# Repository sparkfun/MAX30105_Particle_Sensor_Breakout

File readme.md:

MAX30105 Particle and Pulse Ox Sensor Breakout
=======

A breakout board for the MAX30105 Particle Sensor. This sensor uses three LEDs (Red, Green, IR) to shine different wavelengths of light at any particle in front of the photo detector. Based on the reflection the sensor outputs readings. 

That's my heart beat!

Sensor is capable of detecting pulses but only limited algorithms are provided. It is up to the user to create the algorithms to detect different particles and/or SPO2 and/or do Pulse Detection.

Board requires 3.3V to operate the IR and Red LEDs. 3.5V is recommended to operate the green LED. It has onboard voltage regulation and BSS138 MOSFETs to convert from larger logic voltages (5V) down to the needed 1.8V.

License Information
-------------------

The hardware is released under [Creative Commons Share-alike 4.0](http://creativecommons.org/licenses/by-sa/4.0/).  
The firmware is released under the [Beerware license](http://en.wikipedia.org/wiki/Beerware).

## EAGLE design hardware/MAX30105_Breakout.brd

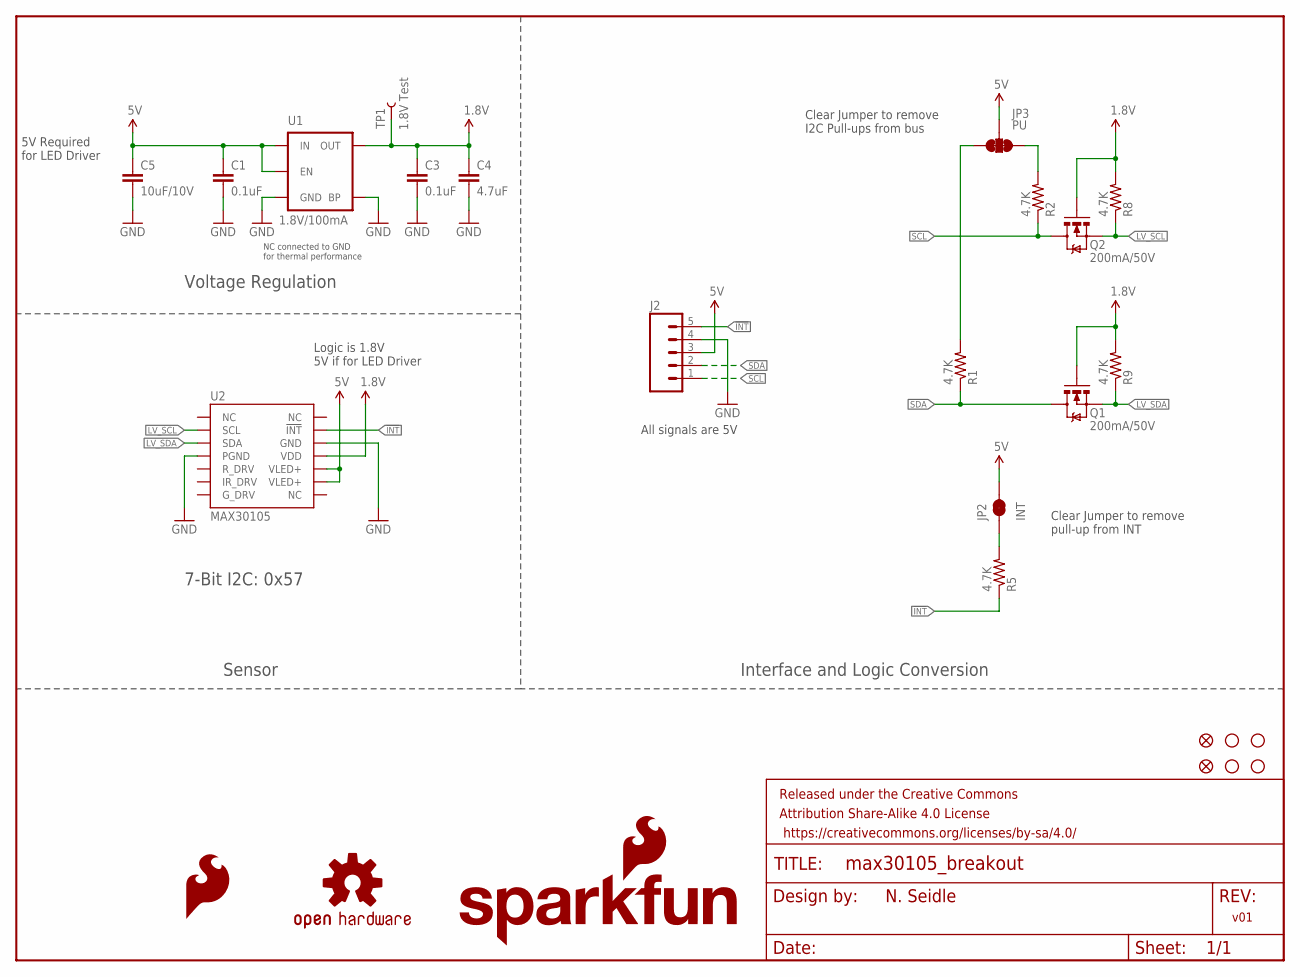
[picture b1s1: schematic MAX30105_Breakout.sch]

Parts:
C1, C3: 0.1uF; 0603-CAP
C4: 4.7uF; 0603-CAP
C5: 10uF/10V; 0805-CAP
FID1, FID2: FIDUCIAL1X2; FIDUCIAL-1X2
FRAME1: FRAME-LETTER; CREATIVE_COMMONS
J2: M05PTH; 1X05
JP2: INT; PAD-JUMPER-2-NC_BY_TRACE_YES_SILK
JP3: PU; PAD-JUMPER-3-3OF3_NC_BY_TRACE_YES_SILK_FULL_BOX
LOGO1: SFE_LOGO_NAME_FLAME.1_INCH; SFE_LOGO_NAME_FLAME_.1
LOGO2: OSHW-LOGOS; OSHW-LOGO-S
LOGO4: SFE_LOGO_FLAME.1EXP; SFE_LOGO_FLAME_COPPER_EXPOSED_.1
Q1, Q2: 200mA/50V; SOT23-3
R1, R2, R5, R8, R9: 4.7K; 0603-RES
STANDOFF1, STANDOFF2, STANDOFF3, STANDOFF4: STAND-OFF
TP1: 1.8V Test; PAD.03X.04
U1: 1.8V/100mA; SC70
U2: MAX30105; OLGA-14

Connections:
1.8V: C3.1, C4.1, Q1.1 (G), Q2.1 (G), R8.2, R9.2, TP1.P$1, U1.5 (OUT), U2.11 (VDD)
5V: C1.1, C5.1, J2.3, JP2.2, JP3.2, U1.1 (IN), U1.3 (EN), U2.9 (VLED+), U2.10 (VLED+)
!INT: J2.5, R5.1, U2.13 (!INT)
GND: C1.2, C3.2, C4.2, C5.2, J2.4, U1.2 (GND), U1.4 (BP), U2.4 (PGND), U2.12 (GND)
LV_SCL: Q2.2 (S), R8.1, U2.2 (SCL)
LV_SDA: Q1.2 (S), R9.1, U2.3 (SDA)
unnamed: JP2.1, R5.2
unnamed: JP3.1, R2.2
unnamed: JP3.3, R1.2
SCL: J2.1, Q2.3 (D), R2.1
SDA: J2.2, Q1.3 (D), R1.1

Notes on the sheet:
7-Bit I2C: 0x57
v01
N. Seidle
Voltage Regulation
Interface and Logic Conversion
Sensor
5V Required for LED Driver
Clear Jumper to remove I2C Pull-ups from bus
Clear Jumper to remove pull-up from INT
Logic is 1.8V 5V if for LED Driver
All signals are 5V
NC connected to GND for thermal performance

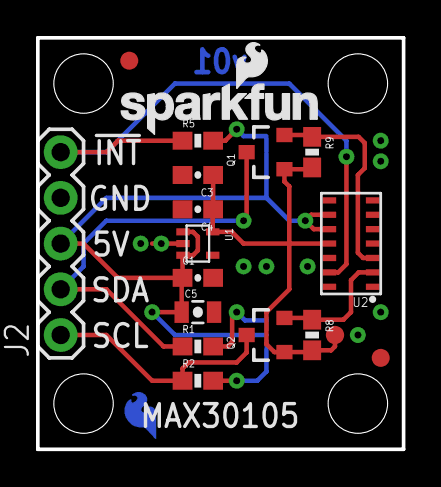
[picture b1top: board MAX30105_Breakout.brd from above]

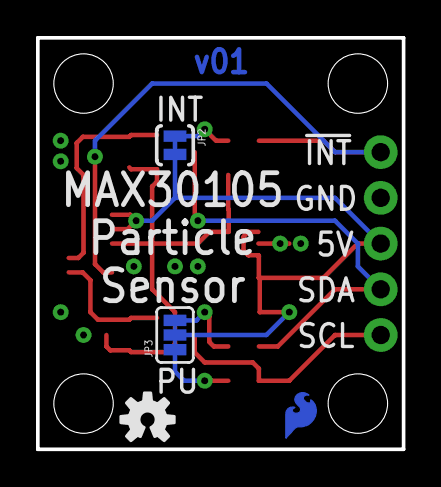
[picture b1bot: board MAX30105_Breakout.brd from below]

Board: 2 copper layers, 20.3 x 22.9 mm, 27 parts (4 on the bottom side), 11 nets.

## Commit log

2016-09-13 :lollipop: Added .gitattributes & .gitignore files
2016-09-13 Adding hardware files.
2016-09-13 Fixes from QC check.
2016-09-13 Mostly cosmetic changes from review.
    Added text to schematic. Changed drill hits to 0.015. Reduced paste pads
    to 75% (roughly) on IC. Created library with only sensor FP.
2016-09-15 Fixed typo in schematic
2016-09-28 Update version to v10
2016-10-20 Adding schematic and images.
2016-11-30 Adding license and library
2016-11-30 Fixing directory structure
2016-11-30 Squashed 'Libraries/Arduino/' content from commit 556c675
    git-subtree-dir: Libraries/Arduino
    git-subtree-split: 556c675a13e3338c9387609c89f57d7b1440020d
2016-11-30 Readme fix.
2016-11-30 Removing duplicate files
2017-08-17 Correct capitalization of Arduino.h
    The filename was incorrectly specified as arduino.h, which causes compilation to fail on filename case sensitive operating systems such as Linux.

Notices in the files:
parts and their libraries:
SparkFun-Aesthetics: Licensing: CC v3.0 Share-Alike You are welcome to use this library for commercial purposes.
SparkFun-Aesthetics: Released under the Creative Commons Attribution Share-Alike 4.0 License
SparkFun-Aesthetics: https://creativecommons.org/licenses/by-sa/4.0
